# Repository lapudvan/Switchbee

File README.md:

# Switchbee
Eclectronics Spring 2019 Final Priject Audrey Lewis and Lauren Pudvan

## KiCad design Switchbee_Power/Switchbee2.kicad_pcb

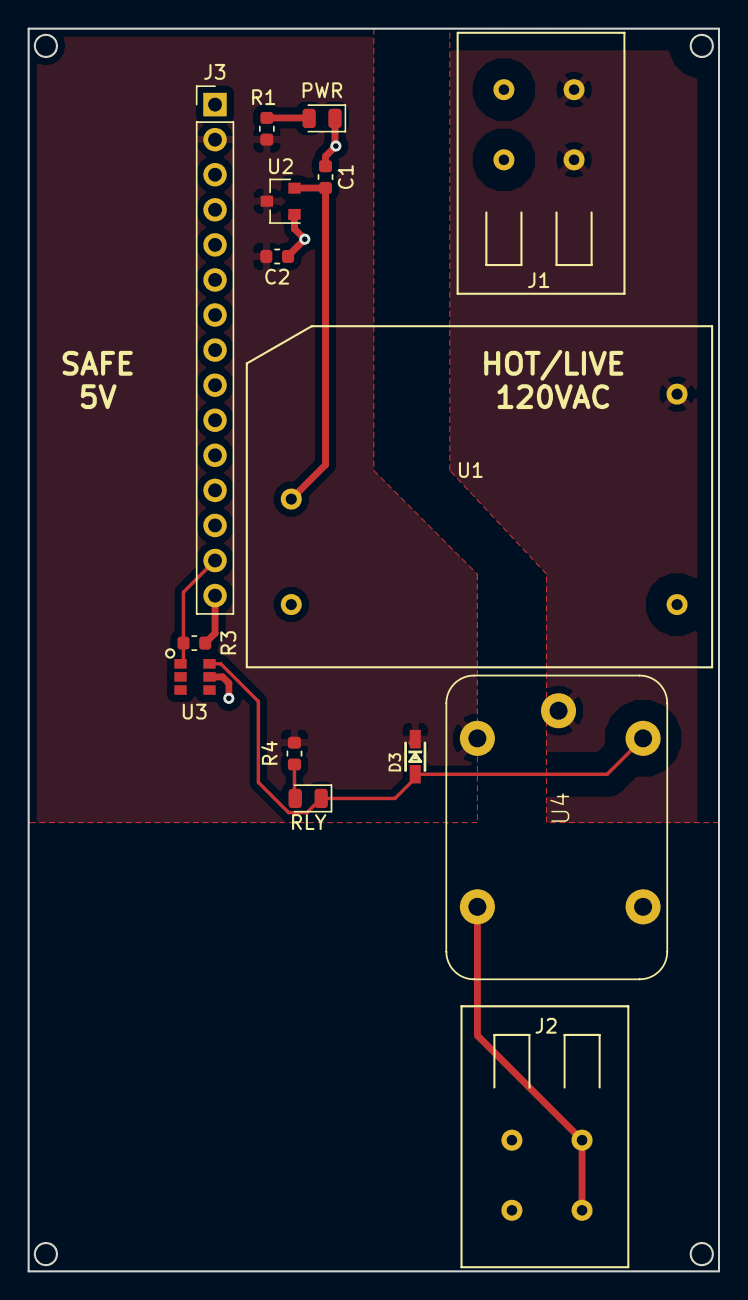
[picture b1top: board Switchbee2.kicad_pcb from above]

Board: 2 copper layers, 50.0 x 90.0 mm, 15 parts (0 on the bottom side), 10 nets.

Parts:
C1, C2: 1µF; C_0603_1608Metric
D3: 1N414B; SOD-323
J1, J2: TermBlock; ED30012-FD
J3: Conn_01x15_Male; PinHeader_1x15_P2.54mm_Vertical
PWR: LED; LED_0805_2012Metric
R1, R4: 1K; R_0603_1608Metric
R3: 10K; R_0603_1608Metric
RLY: LED; LED_0805_2012Metric
U1: RAC02-05SGB; RAC02-05SGB_AC_DC
U2: MCP1702T-5002E_CB; SOT-23
U3: QS6K1TR; mosfet
U4: G5LE-14; RELAY_G5LE-1

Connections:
/5V: C2.1, D3.1, J3.2, R1.1, R4.1, U2.3, U4.2
/GND: C1.2, C2.2, J3.1, J3.15, PWR.1, R3.2, U1.3, U2.1, U3.5
/Signal: J3.14, R3.1, U3.1
/VAC_L: J1.1, U1.1, U4.1
/VAC_N: J1.2, J2.1, U1.2
unnamed: C1.1, U1.4, U2.2
unnamed: PWR.2, R1.2
unnamed: D3.2, RLY.1, U3.6, U4.5
unnamed: R4.2, RLY.2
unnamed: J2.2, U4.3

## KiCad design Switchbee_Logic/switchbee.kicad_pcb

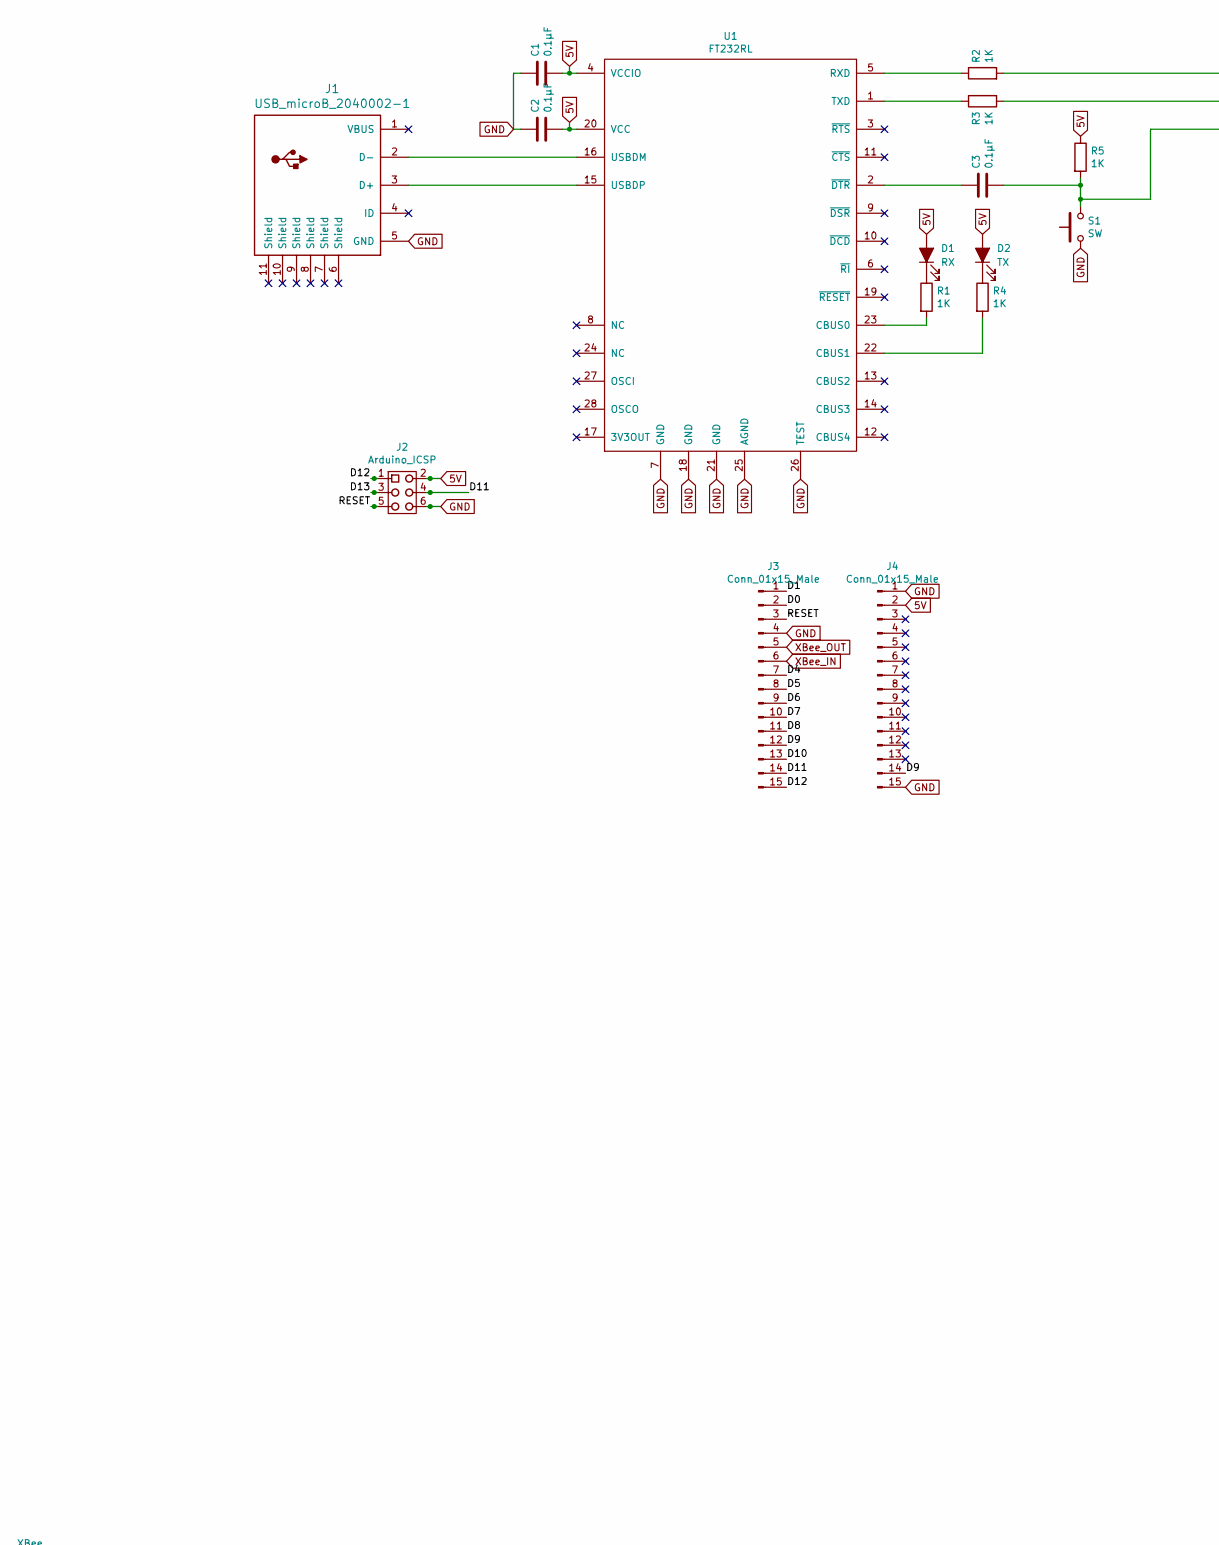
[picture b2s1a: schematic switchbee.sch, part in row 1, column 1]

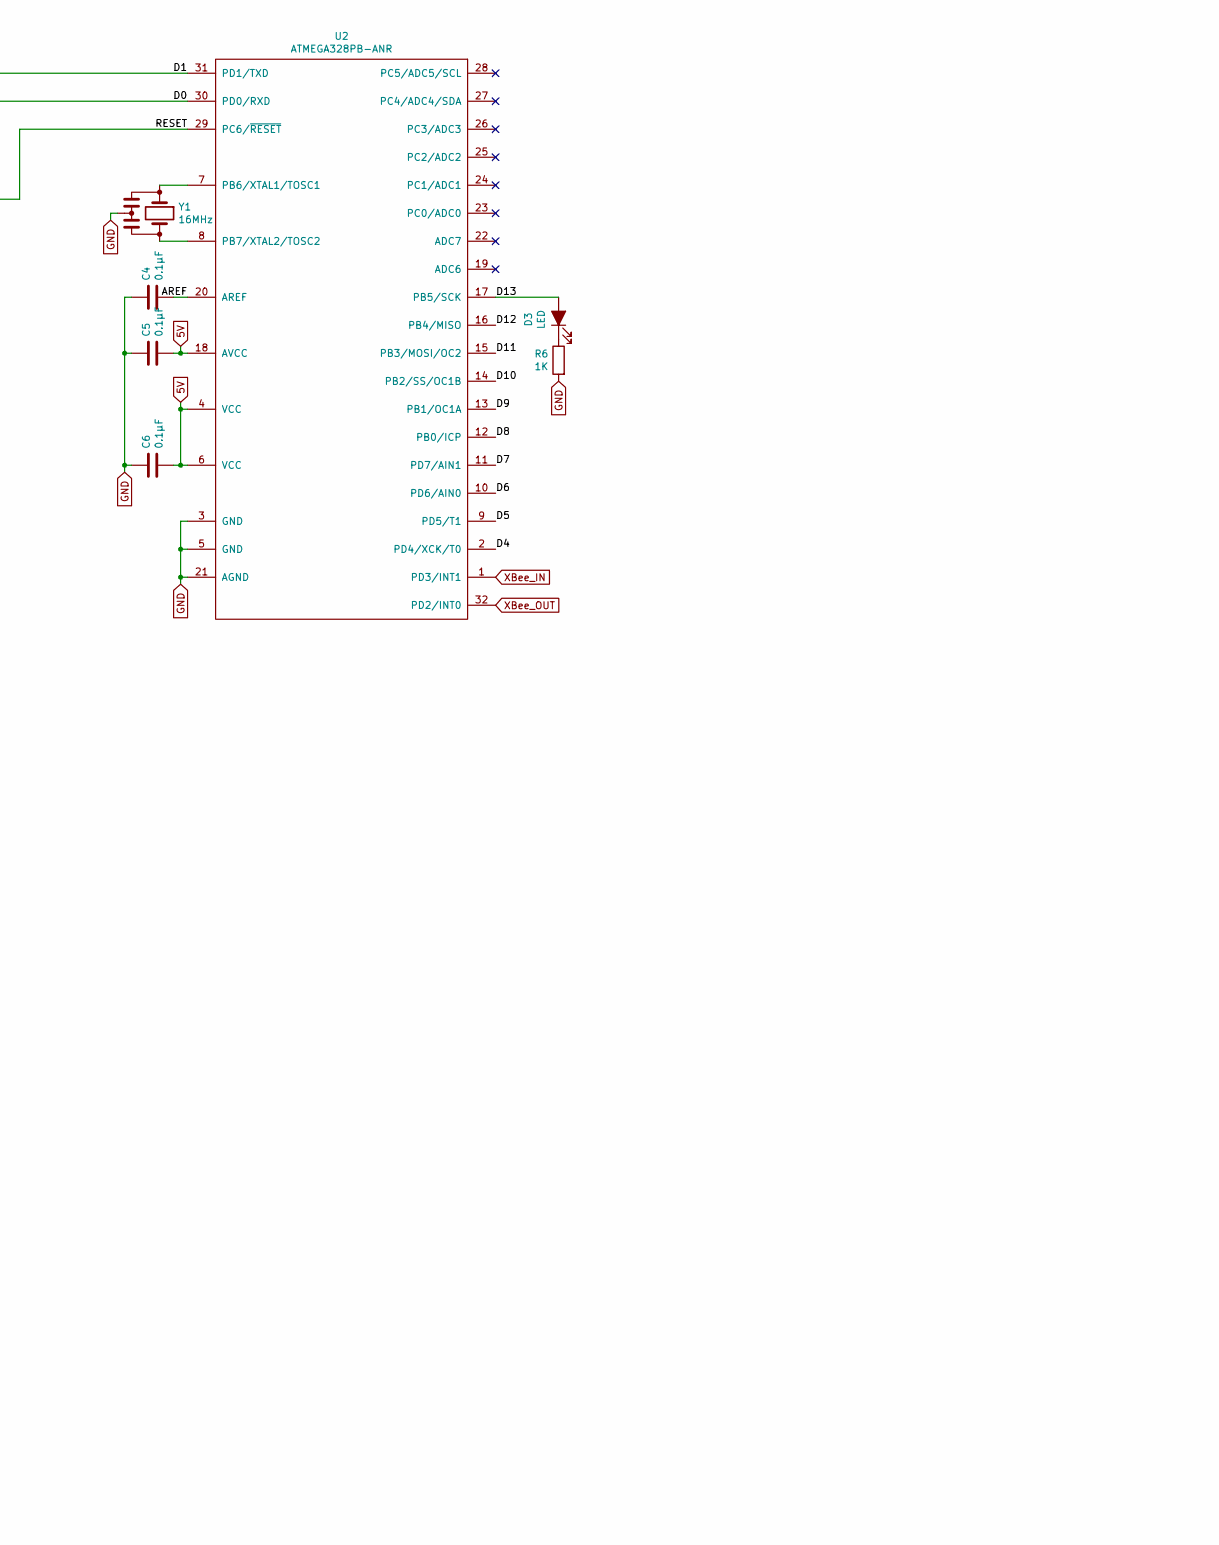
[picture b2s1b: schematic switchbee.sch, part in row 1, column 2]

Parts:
C1, C2, C3, C4, C5, C6: 0.1µF; C_0603_1608Metric
D1: RX; LED_0805_2012Metric
D2: TX; LED_0805_2012Metric
D3: LED; LED_0805_2012Metric
J1: USB_microB_2040002-1
J2: Arduino_ICSP
J3, J4: Conn_01x15_Male; PinHeader_1x15_P2.54mm_Vertical
R1, R2, R3, R4, R5, R6: 1K; R_0603_1608Metric
S1: SW; SW_SPST_B3U-1000P
U1: FT232RL; SSOP-28_5.3x10.2mm_P0.65mm
U2: ATMEGA328PB-ANR; ATmega328
Y1: 16MHz; CSTNE

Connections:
5V: C1.2, C2.2, C5.2, C6.2, D1.2 (A), D2.2 (A), J2.2, J4.2, R5.1, U1.4 (VCCIO), U1.20 (VCC), U2.4 (VCC), U2.6 (VCC), U2.18 (AVCC); also elsewhere on the board
/AREF: C4.2, U2.20 (AREF)
/D0: J3.2, R3.2, U2.30 (PD0/RXD)
/D1: J3.1, R2.2, U2.31 (PD1/TXD)
/D4: J3.7, U2.2 (PD4/XCK/T0)
/D5: J3.8, U2.9 (PD5/T1)
/D6: J3.9, U2.10 (PD6/AIN0)
/D7: J3.10, U2.11 (PD7/AIN1)
/D8: J3.11, U2.12 (PB0/ICP)
/D9: J3.12, J4.14, U2.13 (PB1/OC1A)
/D10: J3.13, U2.14 (PB2/SS/OC1B)
/D11: J2.4, J3.14, U2.15 (PB3/MOSI/OC2)
/D12: J2.1, J3.15, U2.16 (PB4/MISO)
/D13: D3.2 (A), J2.3, U2.17 (PB5/SCK)
/RESET: C3.2, J2.5, J3.3, R5.2, S1.2, U2.29 (PC6/~RESET)
GND: C1.1, C2.1, C4.1, C5.1, C6.1, J1.5 (GND), J2.6, J3.4, J4.1, J4.15, R6.2, S1.1, U1.7 (GND), U1.18 (GND), U1.21 (GND), U1.25 (AGND), U1.26 (TEST), U2.3 (GND), U2.5 (GND), U2.21 (AGND), Y1.2; also elsewhere on the board
unnamed: C3.1, U1.2 (~DTR)
unnamed: D1.1 (K), R1.1
unnamed: D2.1 (K), R4.1
unnamed: D3.1 (K), R6.1
unnamed: J1.2 (D-), U1.16 (USBDM)
unnamed: J1.3 (D+), U1.15 (USBDP)
unnamed: R1.2, U1.23 (CBUS0)
unnamed: R2.1, U1.5 (RXD)
unnamed: R3.1, U1.1 (TXD)
unnamed: R4.2, U1.22 (CBUS1)
unnamed: U2.7 (PB6/XTAL1/TOSC1), Y1.1
unnamed: U2.8 (PB7/XTAL2/TOSC2), Y1.3
XBee_IN: J3.6, U2.1 (PD3/INT1); also elsewhere on the board
XBee_OUT: J3.5, U2.32 (PD2/INT0); also elsewhere on the board

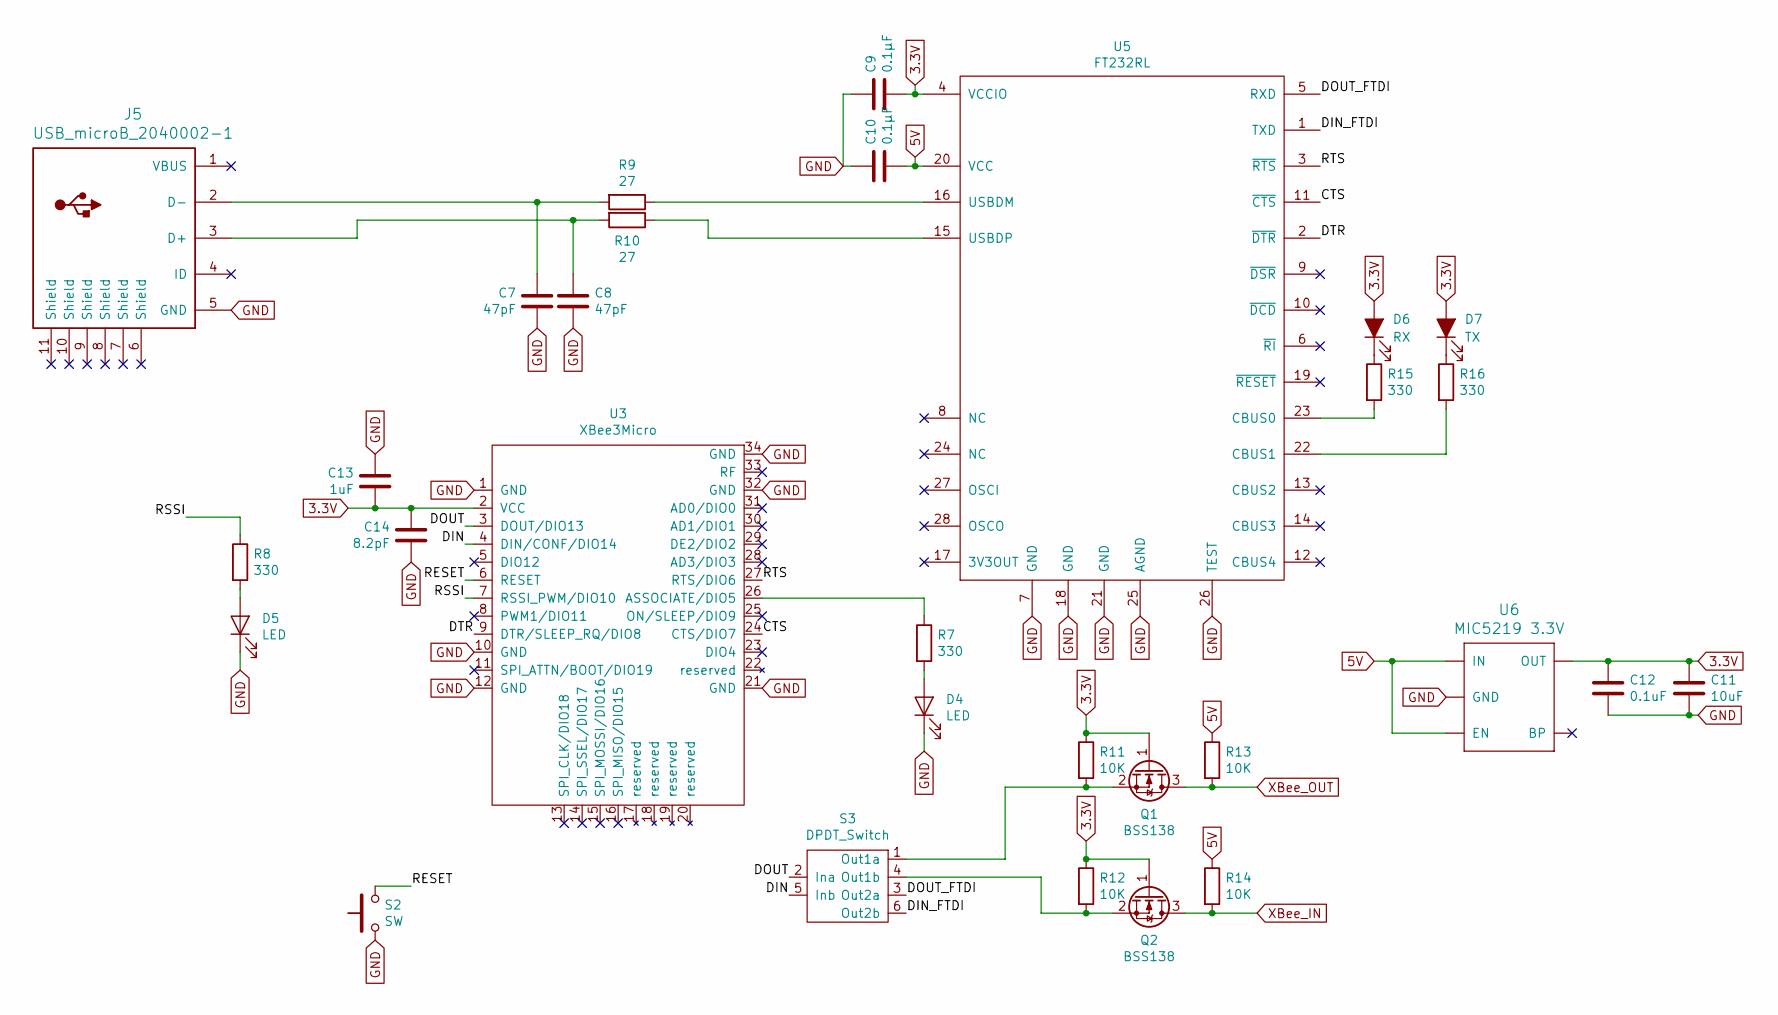
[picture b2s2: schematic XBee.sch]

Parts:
C7, C8: 47pF; C_0603_1608Metric
C9, C10: 0.1µF; C_0603_1608Metric
C11: 10uF; C_0805_2012Metric
C12: 0.1uF; C_0603_1608Metric
C13: 1uF; C_0603_1608Metric
C14: 8.2pF; C_0603_1608Metric
D4, D5: LED; LED_0805_2012Metric
D6: RX; LED_0805_2012Metric
D7: TX; LED_0805_2012Metric
J5: USB_microB_2040002-1
Q1, Q2: BSS138; SOT-23
R7, R8, R15, R16: 330; R_0603_1608Metric
R9, R10: 27; R_0603_1608Metric
R11, R12, R13, R14: 10K; R_0603_1608Metric
S2: SW; SW_SPST_B3U-1000P
S3: DPDT_Switch; JS202011SCQN
U3: XBee3Micro
U5: FT232RL; SSOP-28_5.3x10.2mm_P0.65mm
U6: MIC5219 3.3V; SOT23-5

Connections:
3.3V: C9.2, C11.1, C12.1, C13.2, C14.1, D6.2 (A), D7.2 (A), Q1.1 (G), Q2.1 (G), R11.1, R12.1, U3.2 (VCC), U5.4 (VCCIO), U6.5 (OUT)
5V: C10.2, R13.1, R14.1, U5.20 (VCC), U6.1 (IN), U6.3 (EN); also elsewhere on the board
/XBee/CTS: U3.24 (CTS/DIO7), U5.11 (~CTS)
/XBee/DIN: S3.5 (Inb), U3.4 (DIN/CONF/DIO14)
/XBee/DIN_FTDI: S3.6 (Out2b), U5.1 (TXD)
/XBee/DOUT: S3.2 (Ina), U3.3 (DOUT/DIO13)
/XBee/DOUT_FTDI: S3.3 (Out2a), U5.5 (RXD)
/XBee/DTR: U3.9 (DTR/SLEEP_RQ/DIO8), U5.2 (~DTR)
/XBee/RESET: S2.2, U3.6 (RESET)
/XBee/RSSI: R8.1, U3.7 (RSSI_PWM/DIO10)
/XBee/RTS: U3.27 (RTS/DIO6), U5.3 (~RTS)
GND: C7.2, C8.2, C9.1, C10.1, C11.2, C12.2, C13.1, C14.2, D4.1 (K), D5.1 (K), J5.5 (GND), S2.1, U3.1 (GND), U3.10 (GND), U3.12 (GND), U3.21 (GND), U3.32 (GND), U3.34 (GND), U5.7 (GND), U5.18 (GND), U5.21 (GND), U5.25 (AGND), U5.26 (TEST), U6.2 (GND); also elsewhere on the board
unnamed: C7.1, J5.2 (D-), R9.2
unnamed: C8.1, J5.3 (D+), R10.2
unnamed: D4.2 (A), R7.2
unnamed: D5.2 (A), R8.2
unnamed: D6.1 (K), R15.1
unnamed: D7.1 (K), R16.1
unnamed: Q1.2 (S), R11.2, S3.1 (Out1a)
unnamed: Q2.2 (S), R12.2, S3.4 (Out1b)
unnamed: R7.1, U3.26 (ASSOCIATE/DIO5)
unnamed: R9.1, U5.16 (USBDM)
unnamed: R10.1, U5.15 (USBDP)
unnamed: R15.2, U5.23 (CBUS0)
unnamed: R16.2, U5.22 (CBUS1)
XBee_IN: Q2.3 (D), R14.2; also elsewhere on the board
XBee_OUT: Q1.3 (D), R13.2; also elsewhere on the board

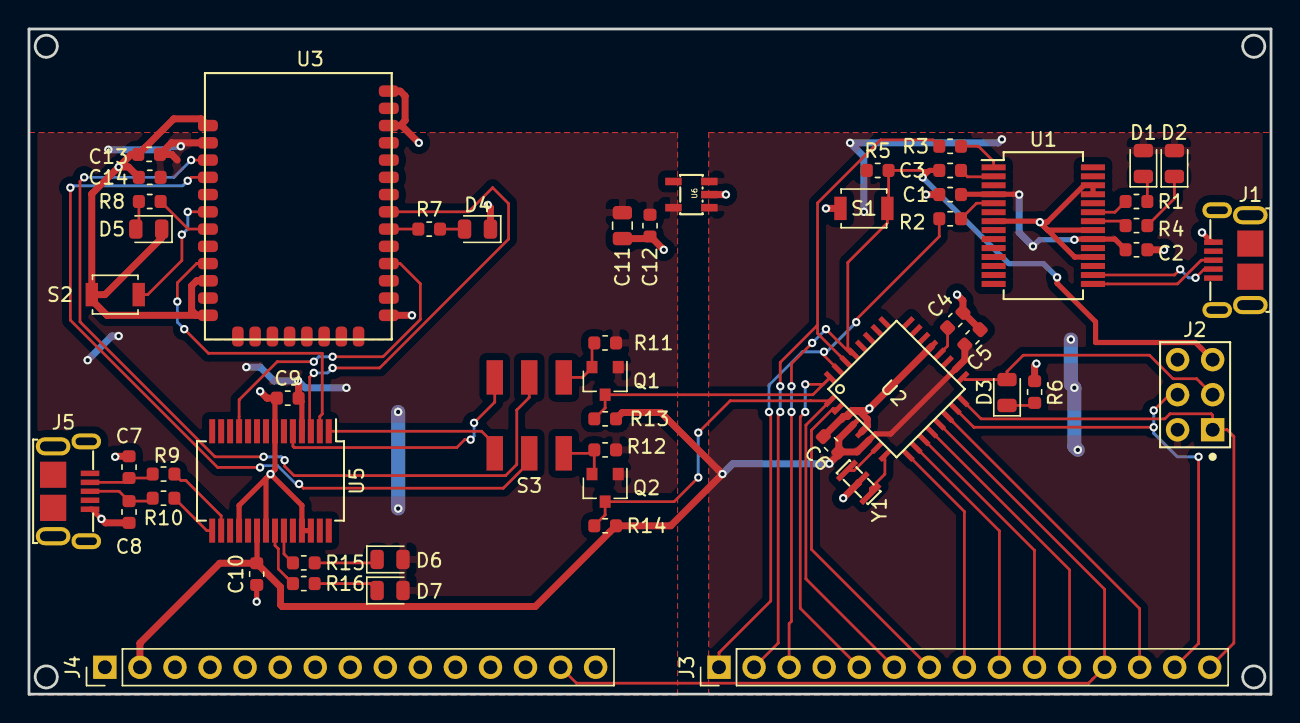
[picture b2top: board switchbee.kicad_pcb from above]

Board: 2 copper layers, 90.0 x 48.2 mm, 53 parts (0 on the bottom side), 53 nets.
